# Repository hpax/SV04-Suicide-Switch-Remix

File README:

Soft-off power button for the Sovol SV04 3D printer, using an RGB LED
pushbutton, a miniature 5V standby power supply module, and an
ATtiny85 microcontroller.

(I used ATtiny85 because I had them on hand. ATtiny25/45 would work
just as well, but seem to be hard to get in DIP8 packages anymore. The
-V versions would work as well, but are typically more expensive.)

The bracket in this tree holds a 16 mm (hole diameter) pushbutton. See
hw/powerctl-sch.pdf for the expected pinout of the connection to the
control board.

Either common anode or common cathode LED buttons can be used: both the
board jumper/connection JP1 and the firmware EEPROM needs to
configured accordingly.

The prebuilt firmware is configured for common anode; for common
cathode, change byte 0 of the EEPROM data file (onoff.eeprom.bin) to
0x28 rather than 0x3b (clear bits 4, 1, 0) or change LED_COMMON_ANODE
in sw/leds.h and recompile.

See the comment near the top of sw/eeprom.h for all the configuration
options can be set using the EEPROM without recompiling.

It is not technically necessary to use an RGB pushbutton. A
one- or two-color pushbutton can be used just as well; the
microcontroller can even dim or pulse the LED(s) if desirable. The
prebuilt firmware uses the LEDs as follows:

	RED	- AC power available, power off
	GREEN	- Button is pressed
	BLUE	- Power on

As the circuit is very simple, I originally used a stripboard rather
than waiting for a custom PCB. However, this turned out to be
mechanically unstable and cracked after a bit. Instead, I ended up
designing a PCB; the design files and a .zip file with CAM files
compatible with JLCPCB (https://jlcpcb.com/) are included. Uploading
that .zip file to their website and they make 5 circuit boards for a
few USD including the cheapest shipping.

The firmware uses avr-gcc and avr-libc; it does not require the
Arduino build environment or boot loader. Note that since all 6 I/O
pins are in use, the RESET DISABLE fuse needs to be programmed, and a
standalone (high voltage) programmer needs to be used. I recommend
socketing the MCU.

If you get a precrimped JST cable you apparently want to be careful
with the pinout (straight or crossover.) I found myself having bought
the latter. The pin that should be connected to the microcontroller
matches the one facing to the REAR of the SV04 mainboard connector J2
(yellow color on the adjacent wires.) Either kind of cable can be
used; simply rotate the connector on the stripboard appropriately.

The silkscreen on the PCB reflects the crossover cable configuration,
since that is what I was using.

Instead of using an SSR, you can opt to upgrade your power supply to
one which supports remote power control. However, most power supplies
are *active low* unlike the SSR, so in that case you will need to
change the polarity of the output in the firmware (or set bit 2 in
byte 0 of the EEPROM); you should also remove resistor R4.

To enable the M81 poweroff G-code command, you need a patch to the
mainboard firmware to define the following options in the Marlin
pinout configuration:

#define SUICIDE_PIN		PE4	/* Connector J2 */
#define SUICIDE_PIN_STATE	LOW

You can use bjoern70's patched firmware:

  https://github.com/Bjoern70/SV04-IDEX-3D-Printer-Mainboard-Source-code

or I have a patch to johncarlson21's Marlin 2.1.x tree:

  https://github.com/hpax/SV04-Marlin-2.1.x.git

Both of those requires the appropriate display firmware update.

Alternatively, adding the above two lines into the file
Marlin/src/pins/stm32f1/pins_CREALITY_V4.h of the stock Sovol firmware
should work too (in which case a display firmware change should not
be necessary as long as you are running the latest one already):

  https://github.com/Sovol3d/SV04-IDEX-3D-Printer-Mainboard-Source-code.git

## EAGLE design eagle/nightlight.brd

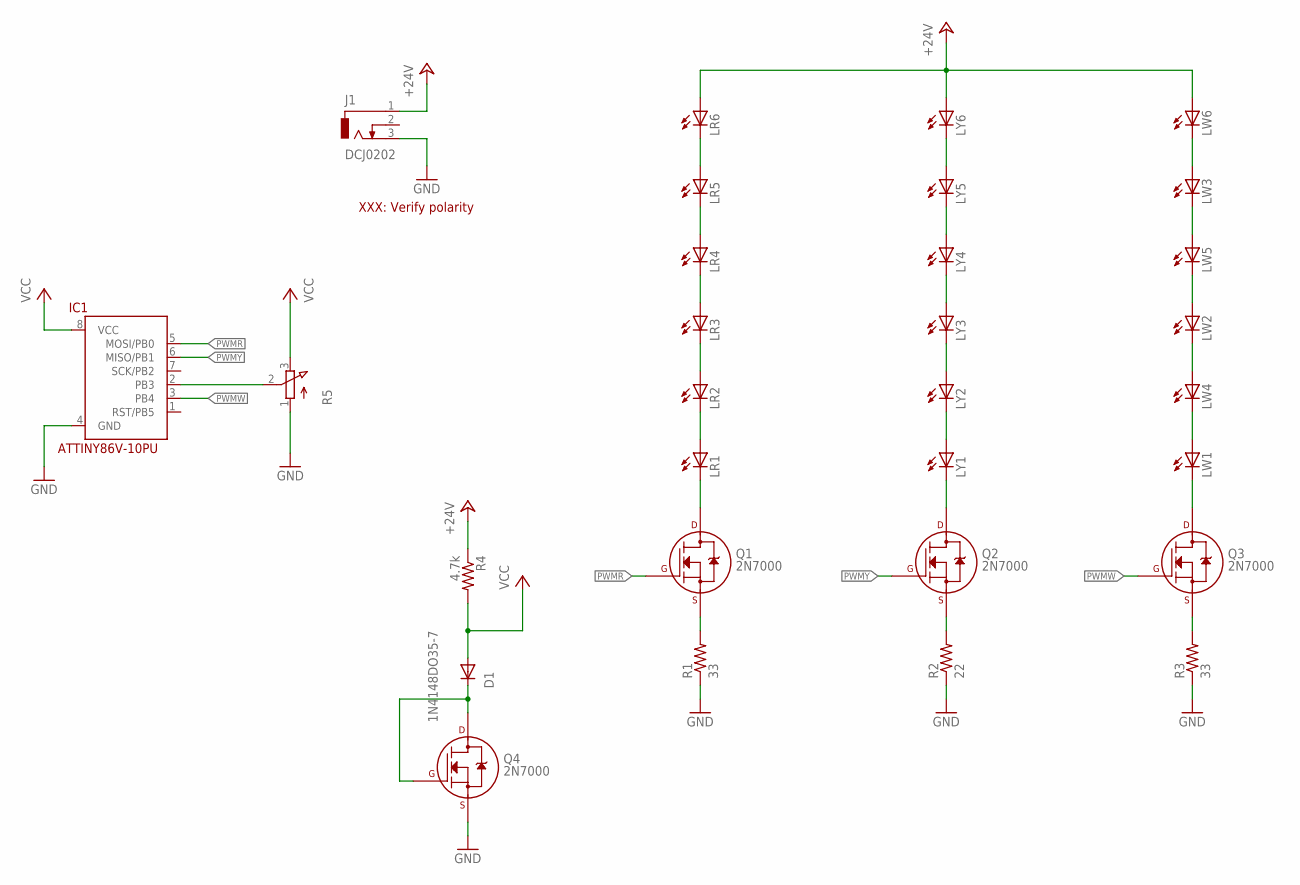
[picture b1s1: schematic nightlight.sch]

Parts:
D1: 1N4148DO35-7; DO35-7
IC1: ATTINY86V-10PU; DIL08
J1: DCJ0202
LR1, LR2, LR3, LR4, LR5, LR6: LED5MM
LW1, LW2, LW3: LED5MM
LW4, LW5, LW6: LED3MM
LY1, LY2, LY3, LY4, LY5, LY6: LED5MM
Q1, Q2, Q3, Q4: 2N7000; TO-92
R1, R3: 33; 0207/10
R2: 22; 0207/10
R4: 4.7k; 0207/10
R5: 3RP/1610N

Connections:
+24V: J1.1, LR6.A, LW6.A, LY6.A, R4.1
GND: IC1.4 (GND), J1.3, Q4.1 (S), R1.1, R2.1, R3.1, R5.1 (A)
unnamed: LR1.K (C), Q1.3 (D)
unnamed: LR1.A, LR2.K (C)
unnamed: LR2.A, LR3.K (C)
unnamed: LR3.A, LR4.K (C)
unnamed: LR4.A, LR5.K (C)
unnamed: LR5.A, LR6.K (C)
unnamed: LY5.A, LY6.K (C)
unnamed: LY4.A, LY5.K (C)
unnamed: LY3.A, LY4.K (C)
unnamed: LY2.A, LY3.K (C)
unnamed: LY1.A, LY2.K (C)
unnamed: LY1.K (C), Q2.3 (D)
unnamed: LW1.K (C), Q3.3 (D)
unnamed: LW1.A, LW4.K (C)
unnamed: LW2.K (C), LW4.A
unnamed: LW2.A, LW5.K (C)
unnamed: LW3.K (C), LW5.A
unnamed: Q1.1 (S), R1.2
unnamed: Q2.1 (S), R2.2
unnamed: Q3.1 (S), R3.2
unnamed: LW3.A, LW6.K (C)
unnamed: D1.C, Q4.2 (G), Q4.3 (D)
unnamed: IC1.2 (PB3), R5.2 (S)
PWMR: IC1.5 (MOSI/PB0), Q1.2 (G)
PWMW: IC1.3 (PB4), Q3.2 (G)
PWMY: IC1.6 (MISO/PB1), Q2.2 (G)
VCC: D1.A, IC1.8 (VCC), R4.2, R5.3 (E)

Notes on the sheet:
XXX: Verify polarity

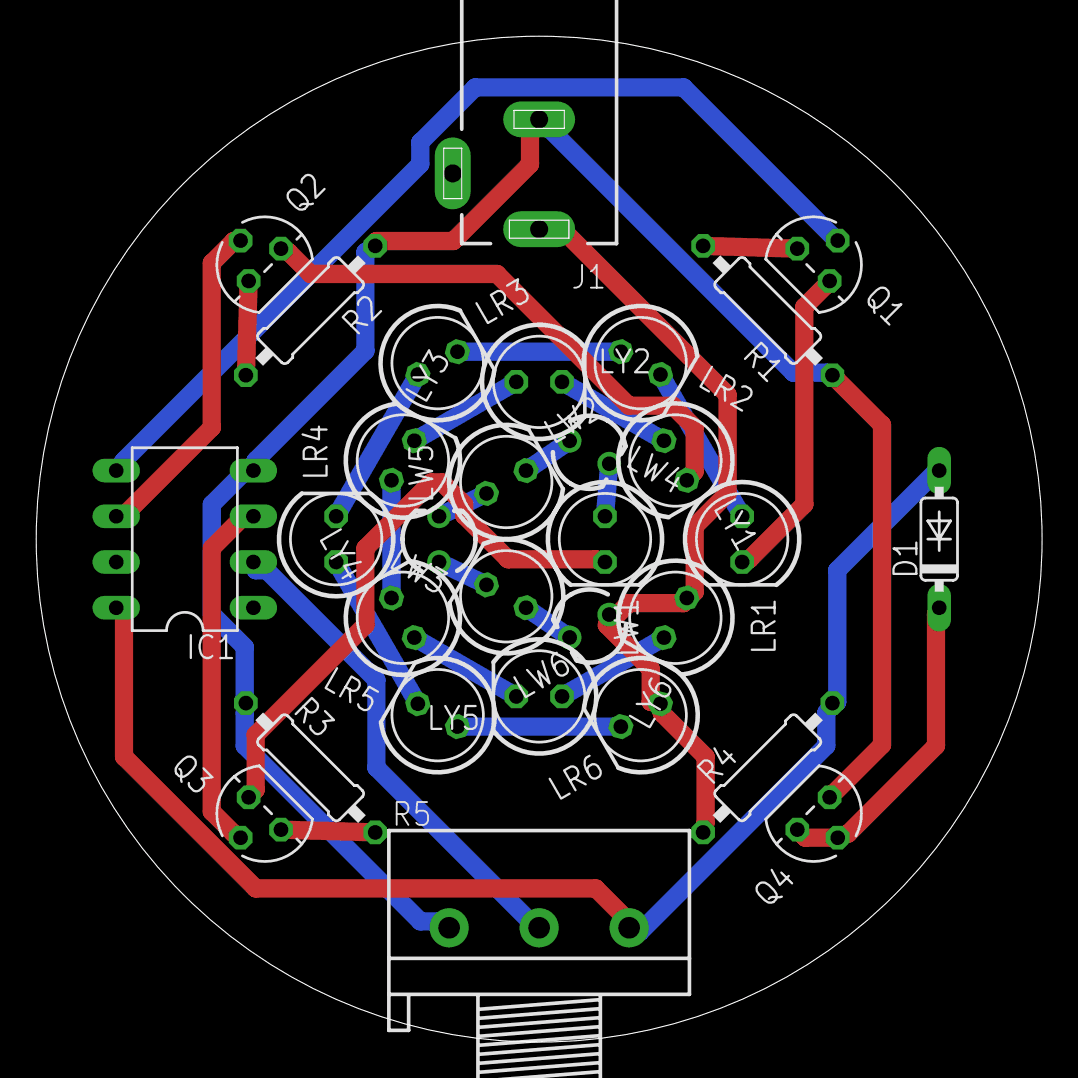
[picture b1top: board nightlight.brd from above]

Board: 2 copper layers, 55.9 x 55.9 mm, 30 parts (0 on the bottom side), 29 nets.

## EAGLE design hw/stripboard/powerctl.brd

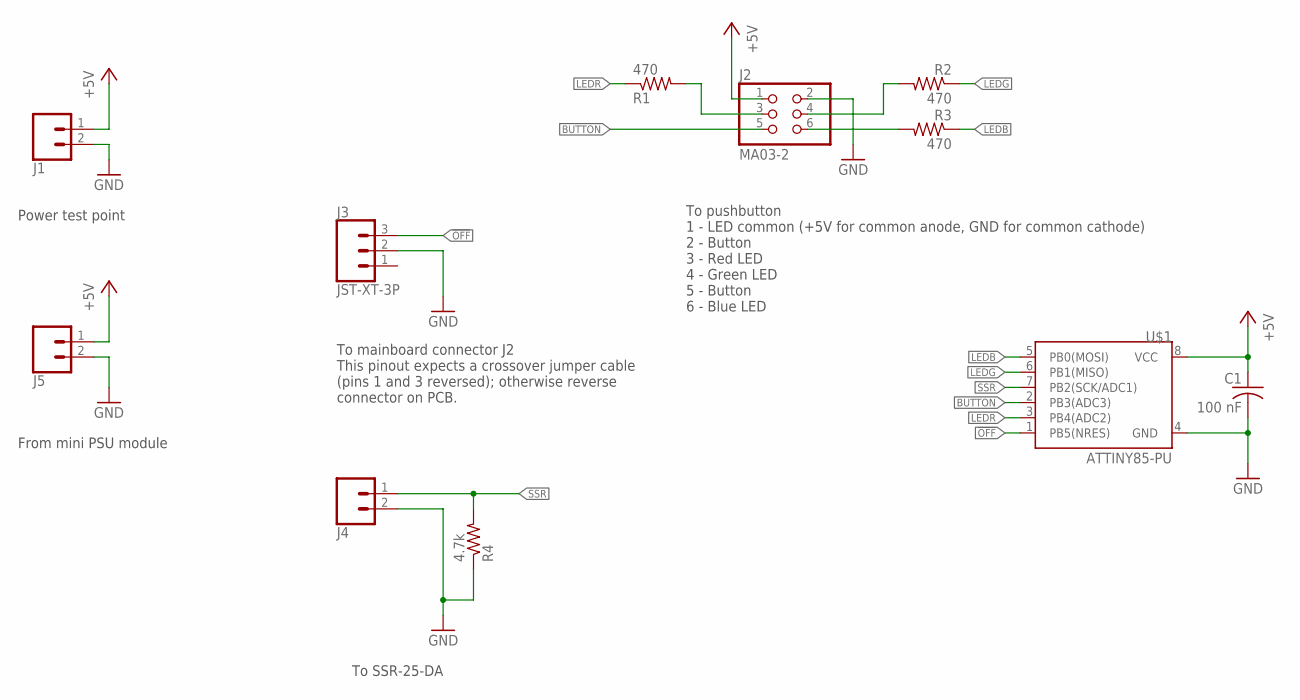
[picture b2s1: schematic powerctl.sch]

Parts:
C1: 100 nF; C025-025X050
J1, J4, J5: CONN_02; 1X02
J2: MA03-2; 2X03
J3: JST-XT-3P; 1X03
R1, R2, R3: 470; 0207/15
R4: 4.7k; 0207/15
U$1: ATTINY85-PU; DIP08

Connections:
!OFF: J3.3, U$1.1 (PB5(NRES))
+5V: C1.1, J1.1, J2.1, J5.1, U$1.8 (VCC)
BUTTON: J2.5, U$1.2 (PB3(ADC3))
GND: C1.2, J1.2, J2.2, J3.2, J4.2, J5.2, R4.1, U$1.4 (GND)
LEDB: R3.1, U$1.5 (PB0(MOSI))
LEDG: R2.1, U$1.6 (PB1(MISO))
LEDR: R1.1, U$1.3 (PB4(ADC2))
unnamed: J2.6, R3.2
unnamed: J2.3, R1.2
unnamed: J2.4, R2.2
SSR: J4.1, R4.2, U$1.7 (PB2(SCK/ADC1))

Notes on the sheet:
From mini PSU module
Power test point
To pushbutton 1 - LED common (+5V for common anode, GND for common cathode) 2 - Button 3 - Red LED 4 - Green LED 5 - Button 6 - Blue LED
To mainboard connector J2 This pinout expects a crossover jumper cable (pins 1 and 3 reversed); otherwise reverse connector on PCB.
To SSR-25-DA

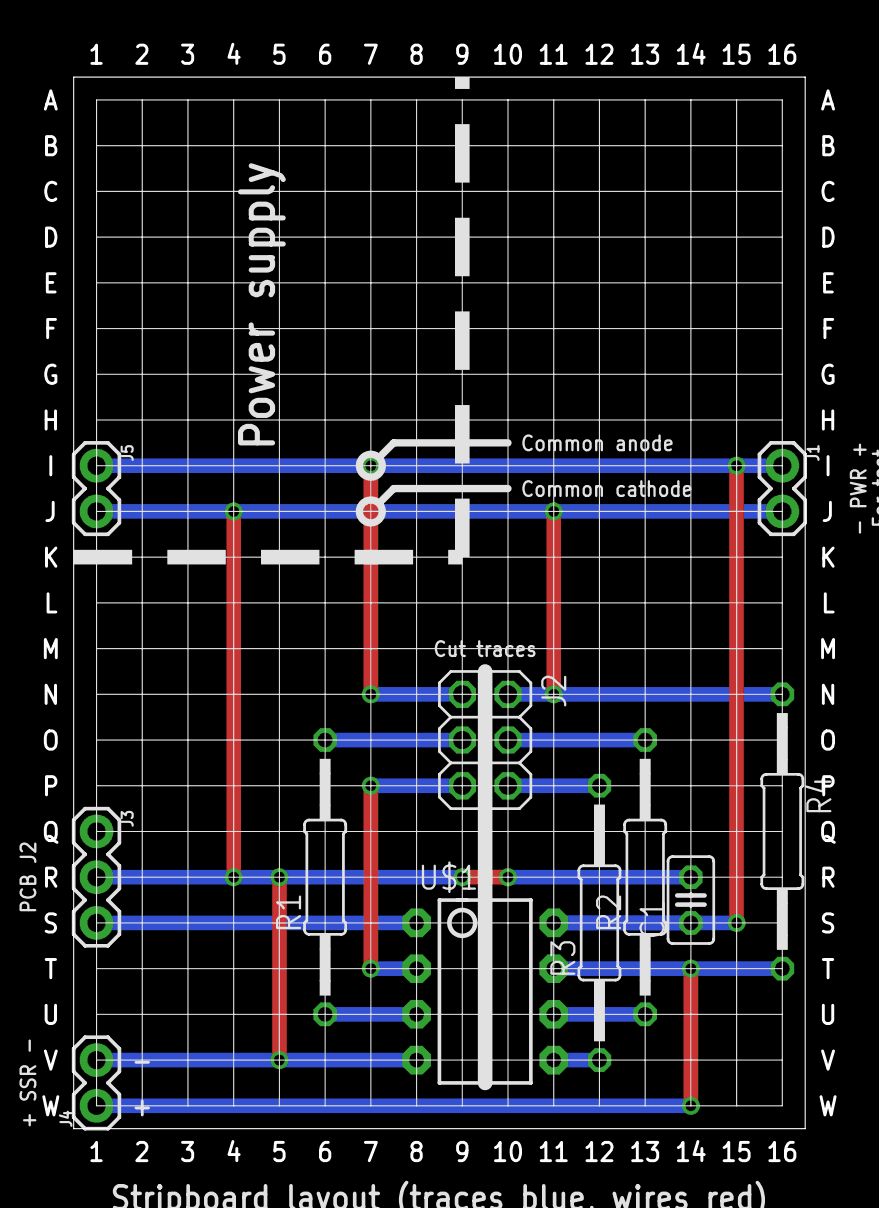
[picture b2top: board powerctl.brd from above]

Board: 2 copper layers, 44.8 x 63.1 mm, 11 parts (0 on the bottom side), 11 nets.

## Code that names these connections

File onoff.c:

#include "util.h"

/* Fuse settings */
FUSES = {
    /* Clock: internal 1 MHz */
    .low	= LFUSE_DEFAULT,
    /* All pins in use as GPIO, no reset/debugwire/SPI programming */
    .high	= FUSE_RSTDISBL,
    /* Self-programming of flash is not used, so disabled */
    .extended	= EFUSE_DEFAULT
};

/* LED intensities */
#define LEDR_PWM	255
#define LEDG_PWM	255
#define LEDB_PWM	255

#define LED_COMMON_ANODE	1

/* Pinmasks - these are PBx port bit numbers, not physical pins! */
#define PIN_OFF		5
#define PINMASK_OFF	(1U << PIN_OFF)
#define PIN_BUTTON	3
#define PINMASK_BUTTON	(1U << PIN_BUTTON)
#define PIN_SSR		2
#define PINMASK_SSR	(1U << PIN_SSR)
#define PINMASK_LEDS	((1U << 0)|(1U << 1)|(1U << 4))

enum led {
    LED_R,
    LED_G,
    LED_B
};

static inline void set_led(enum led led, uint8_t val)
{
    switch (led) {
    case LED_R: OCR1B = val; break;
    case LED_G: OCR0B = val; break;
    case LED_B: OCR0A = val; break;
    }
}

static void init(void)
{
    /* Initializing... */
    cli();

    /* Interrupt control */
    GIMSK = 0;
    PCMSK = 0;

    /*
     * Inputs:
     * OFF#    - PB5 - pin 1 - power off from mainboard
     * BUTTON# - PB3 - pin 2 - pushbutton
     * Outputs:
     * OC1B    - PB4 - pin 3 - red LED	  (active low)
     * OC0A    - PB0 - pin 5 - blue LED   (active low)
     * OC0B    - PB1 - pin 6 - green LED  (active low)
     * SSR     - PB2 - pin 7 - SSR enable (active high)
     *
     * Initially drive everything to its inactive state; enable
     * pullups on inputs.
     */
    PORTB = (uint8_t)~((LED_COMMON_ANODE ? 0 : PINMASK_LEDS)|PINMASK_SSR);
    MCUCR = 0x00;		/* Enable input pullups, sleep mode = idle */
    DDRB  = PINMASK_LEDS|PINMASK_SSR;

    /* Timer interrupt and status */
    TIMSK  = 0;
    TIFR   = 0;

    /* COMxx values */
#define TCRCOM		(LED_COMMON_ANODE ? 3 : 2)

    /*
     * Timer 1 programming
     *
     * HARDWARE ERRATUM: COM1Ax must be = COM1Bx or OC1B PWM output
     * does not work.  Fortunately the PWM from timer 0 seems to take
     * priority on pin PB1.
     */
    /* OC1B enabled, inverted PWM mode;  */
#define GTCCR_CONFIG	((1 << 6) | (TCRCOM << 4))
    /* Bits to be held until after configuration */
#define GTCCR_SYNC	((1 << 7) | (1 << 0))

    GTCCR = GTCCR_CONFIG | GTCCR_SYNC;
    PLLCSR = 0;
    TCCR1 = (1 << 7) | (0 << 6) | (TCRCOM << 4) | (1 << 0);
    OCR1C = 255;		     /* Run from 0 to 255 */

    /*
     * Timer 0 programming
     *
     * OC0A/OC0B are set up in inverting phase correct PWM mode.
     * This gives a dynamic range from (0-255):255.
     */
    TCCR0A = (TCRCOM << 6) | (TCRCOM << 4) | (1 << 0);
    TCCR0B = (0 << 3) | (1 << 0);

    /* Disable all LEDs */
    set_led(LED_R, 0);
    set_led(LED_G, 0);
    set_led(LED_B, 0);

    /* Enable to PWM counters */
    GTCCR = GTCCR_CONFIG;

    /* If we ever do interrupt stuff, should be OK now... */
    sei();
}

static inline bool button_pressed(void)
{
    return !((PINB >> PIN_BUTTON) & 1);
}
static inline bool poweroff_input(void)
{
    return !((PINB >> PIN_OFF) & 1);
}

static void set_button_led(bool button)
{
    set_led(LED_G, button ? LEDG_PWM : 0);
}

static void set_power_led(bool power)
{
    set_led(LED_R, power ? 0 : LEDR_PWM);
    set_led(LED_B, power ? LEDB_PWM : 0);
}

static inline bool power_is_on(void)
{
    return (PORTB >> PIN_SSR) & 1;
}

static void loop(void)
{
    /*
     * Poll both the pushbutton and the power off input with
     * debounce. The power off input is ignored if the power is
     * already off.
     */
    bool power  = power_is_on();
    bool button = button_pressed();

    /* Debounce counters */
    unsigned int button_ctr   = button ? 32768UL : 0;
    unsigned int poweroff_ctr = 0;
    unsigned int poweron_ctr  = 0; /* Time after poweron until OFF valid  */

    const unsigned int button_ctr_incr = 65536ULL/256;
    const unsigned int button_ctr_decr = 65536ULL/16;

    const unsigned int poweroff_incr   = 65536ULL/256;
    const unsigned int poweron_incr    = 1;

    set_power_led(power);
    set_button_led(button);

    while (true) {
	if (button_pressed()) {
	    if (button_ctr <= ~button_ctr_incr) {
		button_ctr += button_ctr_incr;
	    } else if (!button) {
		set_button_led(button = true);
		set_power_led(power = !power);
		PINB = PINMASK_SSR; /* Toggle SSR output */
	    }
	} else {
	    if (button_ctr >= button_ctr_decr) {
		button_ctr -= button_ctr_decr;
	    } else if (button) {
		set_button_led(button = false);
	    }
	}

	if (power) {
	    if (poweron_ctr <= ~poweron_incr) {
		poweron_ctr += poweron_incr;
	    }
	} else {
	    poweron_ctr = 0;
	}

	if (poweron_ctr > ~poweron_incr) {
	    if (poweroff_input()) {
		if (poweroff_ctr <= ~poweroff_incr) {
		    poweroff_ctr += poweroff_incr;
		} else if (power) {
		    set_power_led(power = false);
		    PORTB &= ~PINMASK_SSR;
		}
	    } else {
		if (poweroff_ctr >= poweroff_incr) {
		    poweroff_ctr -= poweroff_incr;
		}
	    }
	} else {
	    poweroff_ctr = 0;
	}
    }
}

static inline void delay(unsigned int multiplier)
{
    _delay_ms(multiplier * 2);
}

static void test_leds(void)
{
    struct rgbs {
	int8_t r, g, b;
    };
    static const struct rgbs fades[] = {
	{ +1,  0,  0 },		/* K > R */
	{  0, +1,  0 },		/* R > Y */
	{ -1,  0,  0 },		/* Y > G */
	{  0,  0, +1 },		/* G > C */
	{  0, -1,  0 },		/* C > B */
	{ +1,  0,  0 },		/* B > M */
	{  0, +1,  0 },		/* M > W */
	{ -1, -1, -1 }		/* W > K */
    };
    uint8_t r, g, b;

    set_led(LED_R, r = 0);
    set_led(LED_G, g = 0);
    set_led(LED_B, b = 0);

    for (uint8_t n = 0; n < 8; n++) {
	const struct rgbs *fade = fades;
	for (uint8_t nf = 0; nf < ARRAY_SIZE(fades); nf++) {
	    int8_t dr = fade->r;
	    int8_t dg = fade->g;
	    int8_t db = fade->b;
	    fade++;
	    for (uint8_t i = 1; i; i++) {
		delay(1);
		set_led(LED_R, r += dr);
		set_led(LED_G, g += dg);
		set_led(LED_B, b += db);
	    }
	}
    }

    delay(32);
}

int main(void)
{
    init();
    if (button_pressed())
	test_leds();
    loop();
}

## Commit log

2018-01-27 Sample Makefile
2018-01-27 More automation, including dependency generation
2018-01-27 Makefile: with proper dependencies, don't need $(HEADERS)
2018-01-27 Makefile: pad programming binaries
2018-01-27 Actual tinyflash project
2018-01-27 Makefile: beginnings of a flashing infrastructure
2018-01-28 Makefile: don't try to flash a zero-length file
2018-01-28 Use PWM output to control brightness
2018-01-28 tinyflash: use ADC to receive input via potentiometer
2018-01-28 Move work to ADC interrupt handler, let the CPU sleep
    Put the CPU into idle sleep when we are not doing anything, let the
    PWM and ADC units do the work themselves.
2018-01-28 Increase the total darkness guard band to 64
2018-05-05 Rename tinyflash -> nightlight
2018-05-05 Add hardware files
2018-05-05 Additional hardware files: compute LED positions
2018-05-05 One more tinyflash -> nightlight
2018-05-05 Avoid pullups, reduce guard band size
2019-04-03 Makefile: at least ATTiny85V seems to fail to verify EEPROM
2019-04-03 Add detection of knob limits into EEPROM
2019-04-03 Rename nightlight.h to util.h
2019-04-03 Add util.h from nightlight project; probably useful in general
2024-06-15 3D printer on/off system
2024-06-16 Make and flash the efuses
2024-06-16 onoff.c: fix LED configuration and pin assignments; add LED test
    Fix the LED configuration and the pin assignments.
    If the button is pressed during power on, cycle through colors 8 times
    through the extended rainbow as an LED test before assuming normal
    operation.
2024-06-16 eagle: add schematic (.sch and .pdf)
    No board file since a veroboard was used.
2024-06-16 Rename eagle -> hw
    More appropriate naming of the directory with hardware info.
2024-06-16 Some completely unnecessary optimizations
    For the sheer fun of seeing the resulting AVR code...
2024-06-19 Add fuses.conf to zipfile; add firmware snapshot
2024-06-19 bracket: add 3D model for bracket
2024-06-19 hw: update hardware, including warning about JST jumper cable
    Update the hardware schematic to indicate the pinout for the button
    connector, and note the oddness with the apparent commonness(???) of
    JST jumper cable crossover cables.
2024-06-19 Move sw (firmware) sources to a subdirectory
2024-06-19 Add README for the bracket
2024-06-19 Specify 16 mm pushbutton
2024-06-19 README: RGB is not mandatory
2024-06-20 Update schematic and add stripboard layout
2024-06-20 Add images of wiring and case mounting
2024-06-20 Add images for the bracket; move README to the top.
2024-06-20 README: document build environment
2024-06-20 README: document default LED configuration
2024-06-20 README: watch out for JST polarity
2024-06-20 README: add documentation for using a controllable power supply
    Most controllable power supplies are active low, whereas the SSR is
    active high.
2024-06-24 README: document where to get mainboard firmware; rename firmware.zip
    Document where to get updated firmware for the mainboard.
    Rename firmware.zip to firmware-attiny85.zip to avoid confusion with
    the mainboard firmware.
2024-06-25 sw: move LED test fade table to progmem
    No reason to put that in RAM...
2024-08-25 User friendliness improvements; PWM for LEDs
    - Pulse red LED after power loss
    - Minimum time for button press recognition
    - Very long button press to cancel
2024-08-25 hw: add PCB hardware definition and CAM files
2024-08-25 Update prebuilt firmware image
2024-08-25 Update mounting images with PCB images
2024-08-25 sw: move configuration to EEPROM
    Move most of the configuration to EEPROM. This would make it easier
    for a user to modify the configuration by hand rather than rebuilding
    the firmware if they don't have the tools.
2024-08-25 Correctly use EEPROM variables; update README
    Use the EEPROM configurables in all relevant places. Update the README
    to inform about PCB and settable EEPROM configuration values.
2024-08-25 README: any ATtiny25/45/85(V) would work
    Any member of the ATtiny25/45/85 including the V versions work just
    fine in this design.
2024-08-29 sw: better eeprom documentation, fix off signal timer, move sleep
    - Document the EEPROM contents in detail in sw/eeprom.h
    - The OFF signal timer should run from the moment power is applied
    to the SSR, not from when AC power is first applied,
    and should be reset whenever the power is disabled.
    - Move the sleep instruction to the top of the loop, so that a
    continue; statement doesn't bypass it.
2024-08-29 README: add more details
    Add more details about the EEPROM, the LEDs, and the JST connector.
2024-08-29 hw: add bill of materials
2024-08-29 hw: add image and drawing of WX-DC12003
2024-08-29 Update the firmware build
2024-08-29 BOM: add SSR-25-DA
2024-08-29 BOM: add C1
    C1 was missing from the BOM
2024-08-29 BOM: add mounting screws and T-nuts for bracket
2024-08-29 wiring.jpg: note optional ground on center AC pin
2024-08-29 BOM: add mounting screws for SSR, more explicit requirements

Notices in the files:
parts and their libraries:
SparkFun-Connectors: Licensing: Creative Commons ShareAlike 4.0 International - https://creativecommons.org/licenses/by-sa/4.0
